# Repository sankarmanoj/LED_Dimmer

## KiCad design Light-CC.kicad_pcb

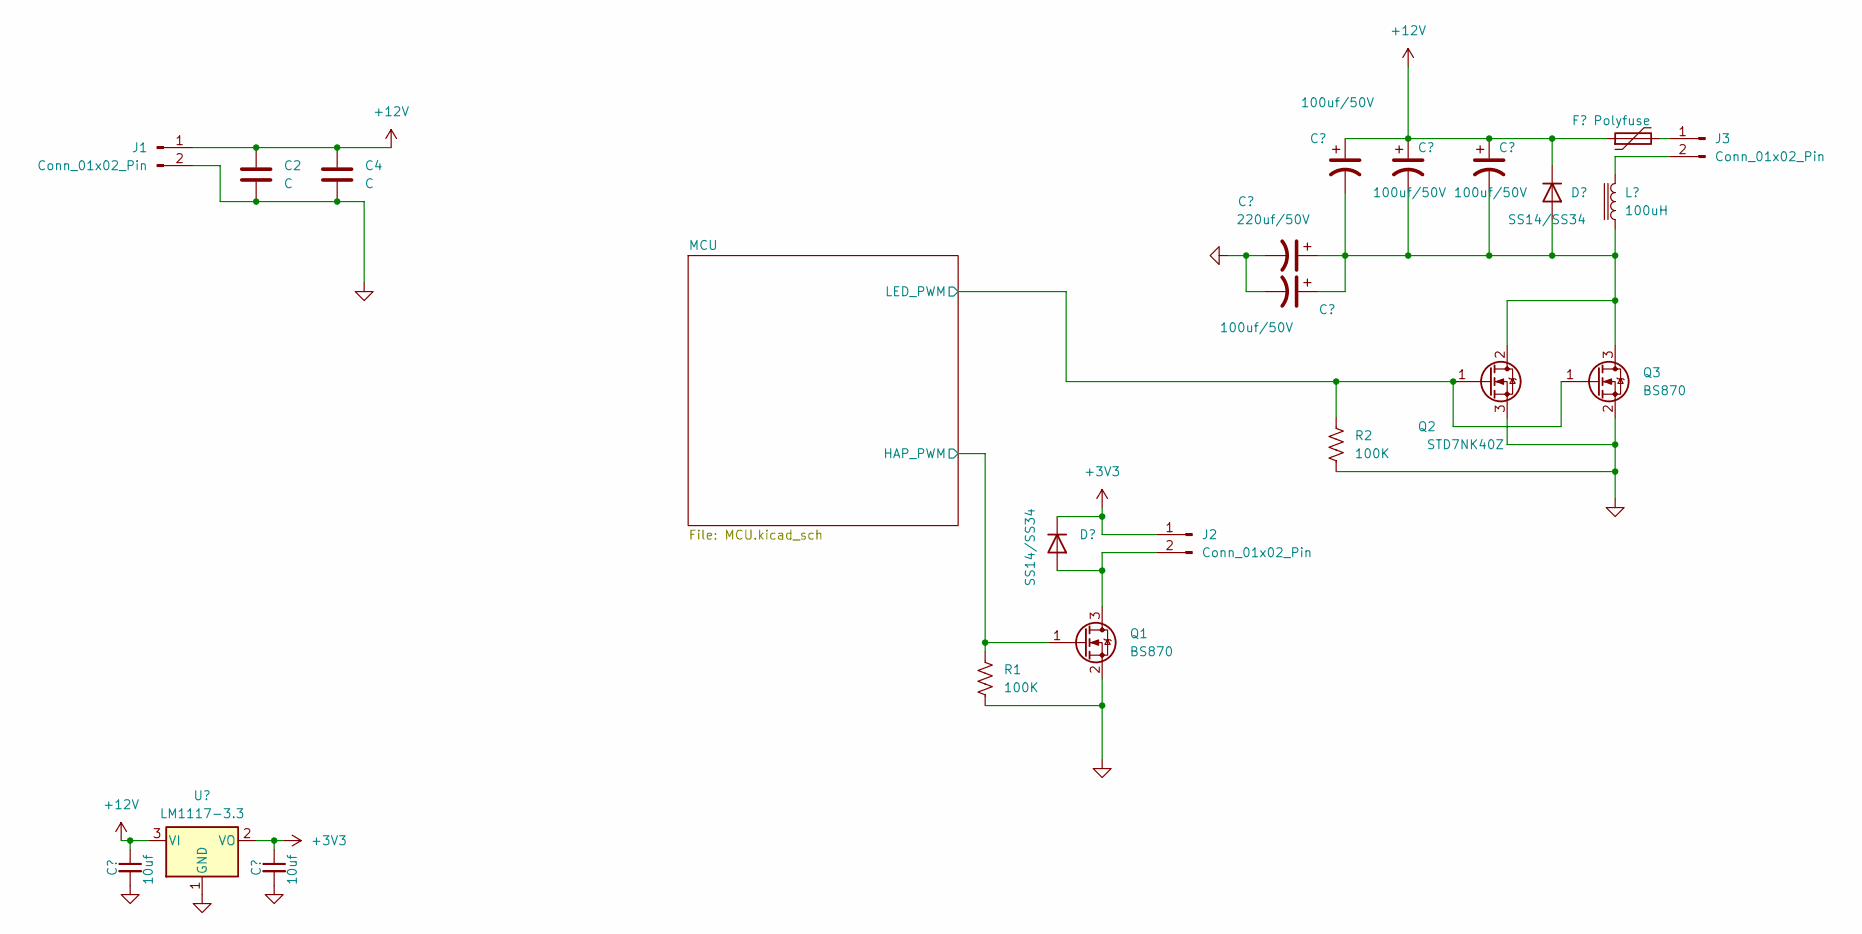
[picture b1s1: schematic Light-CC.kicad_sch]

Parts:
C1, C3: 10uf; C_0805_2012Metric
C2, C4: C; C_0805_2012Metric
C5: 220uf/50V; C_1206_3216Metric
C6, C9: 100uf/50V; C_1206_3216Metric
C7, C8: 100uf/50V; CP_Radial_D5.0mm_P2.50mm
D1, D2: SS14/SS34; D_SMA
F1: Polyfuse; Fuse_1206_3216Metric
J1, J3: Conn_01x02_Pin; SolderWire-0.75sqmm_1x02_P7mm_D1.25mm_OD3.5mm
J2: Conn_01x02_Pin; SolderWire-0.1sqmm_1x02_P3.6mm_D0.4mm_OD1mm_Relief
L1: 100uH; L_Bourns_SRR1260
Q1, Q3: BS870; SOT-23
Q2: STD7NK40Z; TO-252-2
R1, R2: 100K; R_0805_2012Metric
U1: LM1117-3.3; SOT-223-3_TabPin2

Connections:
+3V3: C3.1, D1.1 (K), J2.1, U1.2 (VO); also elsewhere on the board
+12V: C1.1, C2.1, C4.1, C7.1, C8.1, C9.1, D2.1 (K), F1.1, J1.1, U1.3 (VI)
/MCU/HAP_PWM: Q1.1 (G), R1.1; also elsewhere on the board
/MCU/LED_PWM: Q2.1 (G), Q3.1 (G), R2.1; also elsewhere on the board
GND: C1.2, C2.2, C3.2, C4.2, C5.2, C6.2, J1.2, Q1.2 (S), Q2.3 (S), Q3.2 (S), R1.2, R2.2, U1.1 (GND); also elsewhere on the board
unnamed: D1.2 (A), J2.2, Q1.3 (D)
unnamed: C5.1, C6.1, C7.2, C8.2, C9.2, D2.2 (A), L1.1, Q2.2 (D), Q3.3 (D)
unnamed: F1.2, J3.1
unnamed: J3.2, L1.2

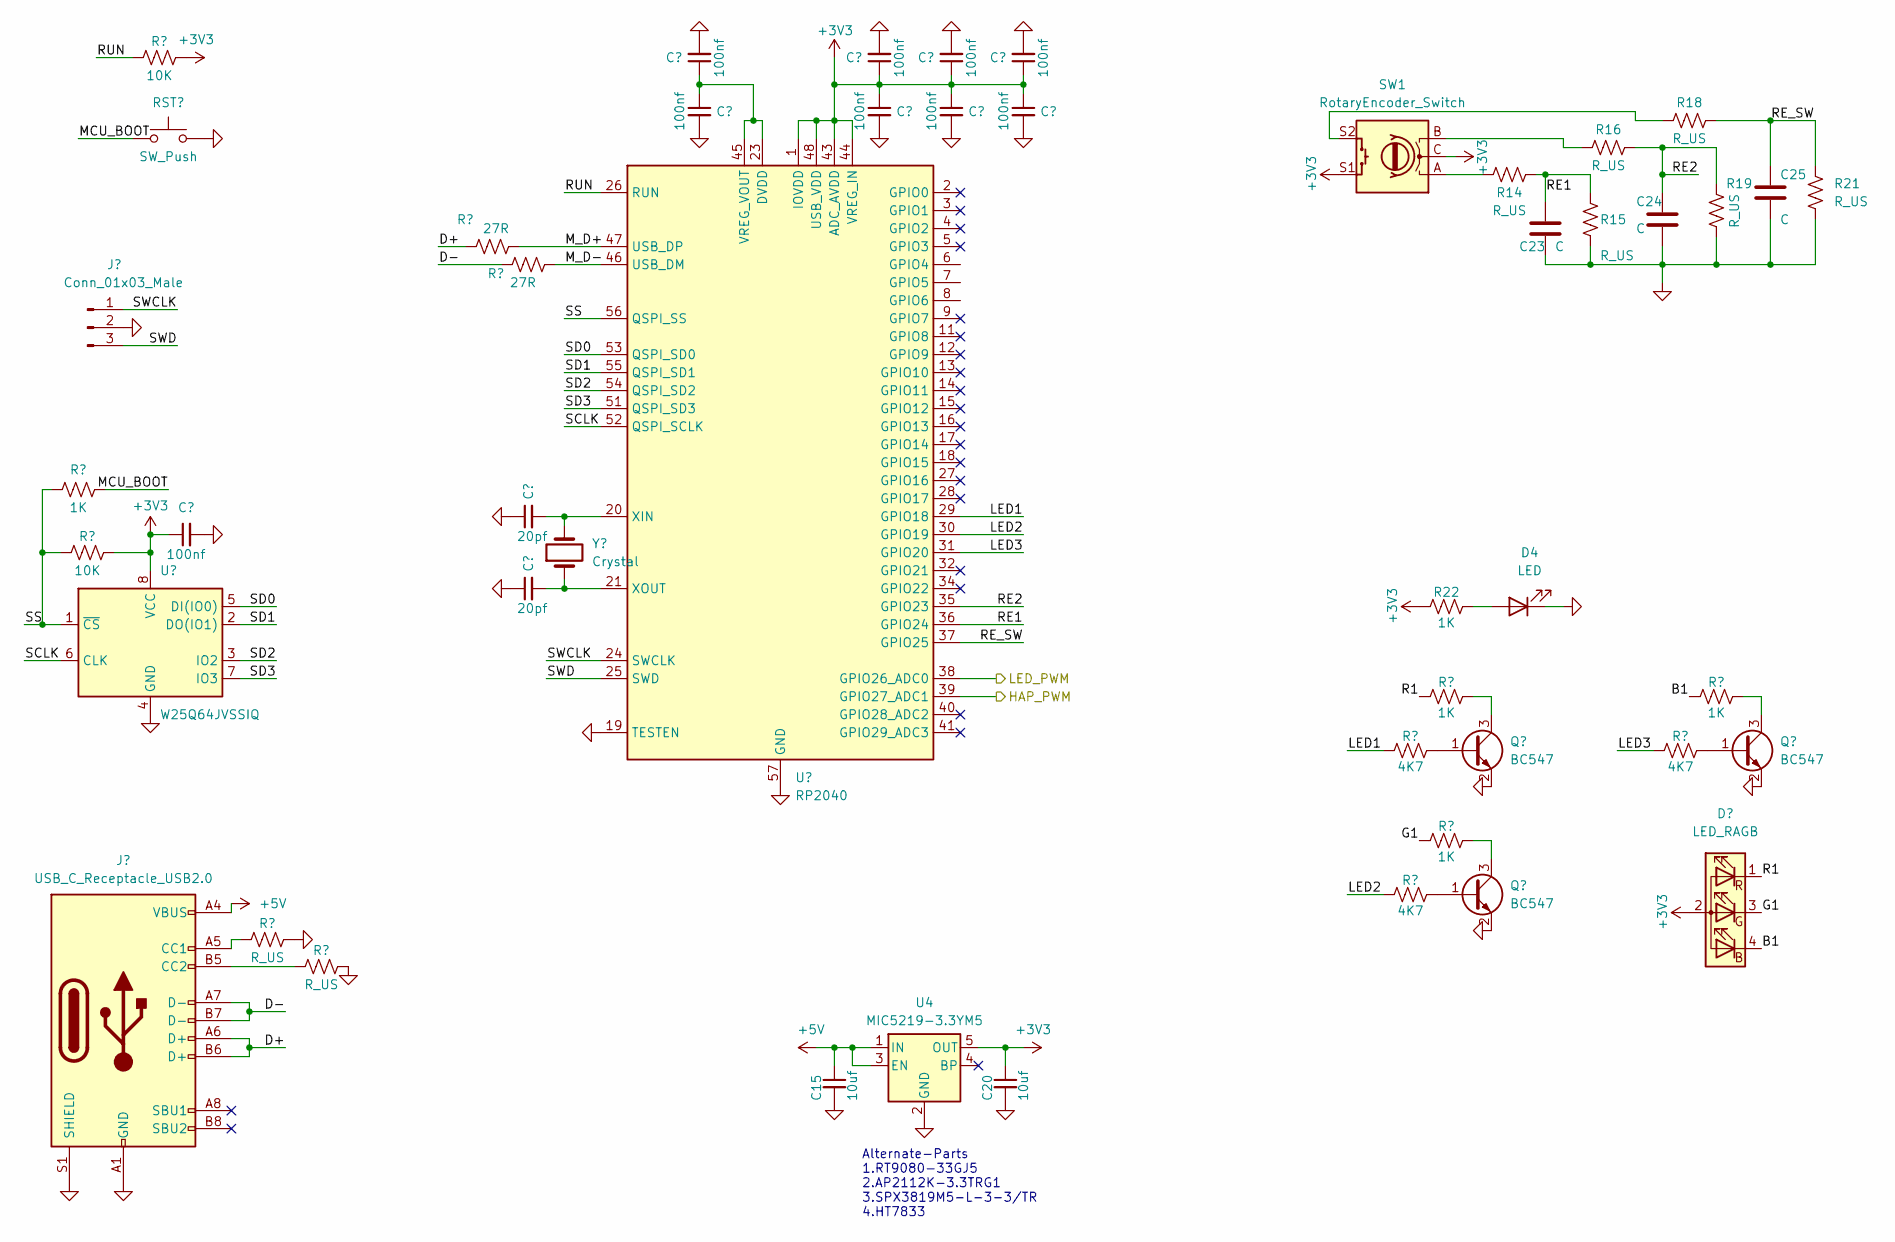
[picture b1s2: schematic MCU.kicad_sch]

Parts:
C10, C13, C14, C16, C17, C18, C19, C21, C22: 100nf; C_0603_1608Metric
C11, C12: 20pf; C_0603_1608Metric
C15, C20: 10uf; C_0805_2012Metric
C23, C24, C25: C; C_0603_1608Metric
D3: LED_RAGB; LED_D5.0mm-4_RGB_Wide_Pins
D4: LED
J4: Conn_01x03_Male; PinHeader_1x03_P2.54mm_Vertical
J5: USB_C_Receptacle_USB2.0; USB_C_Receptacle_Palconn_UTC16-G
Q4, Q5, Q6: BC547; SOT-23
R3, R12, R13, R20, R22: 1K; R_0603_1608Metric
R4, R5: 10K; R_0603_1608Metric
R6, R7, R14, R15, R16, R18, R19, R21: R_US; R_0603_1608Metric
R8, R9: 27R; R_0603_1608Metric
R10, R11, R17: 4K7; R_0603_1608Metric
RST1: SW_Push; SW_SPST_SKQG_WithStem
SW1: RotaryEncoder_Switch; RotaryEncoder_Alps_EC12E-Switch_Vertical_H20mm
U2: W25Q64JVSSIQ; SOIC-8_5.23x5.23mm_P1.27mm
U3: RP2040; QFN-56-1EP_7x7mm_P0.4mm_EP3.2x3.2mm
U4: MIC5219-3.3YM5; SOT-23-5
Y1: Crystal; Crystal_HC49-4H_Vertical

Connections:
+3V3: C10.1, C16.1, C17.1, C18.1, C19.1, C20.1, C21.1, C22.1, D3.2 (A), R4.2, R5.2, R22.1, SW1.C, SW1.S1, U2.8 (VCC), U3.1 (IOVDD), U3.10 (IOVDD), U3.22 (IOVDD), U3.33 (IOVDD), U3.42 (IOVDD), U3.43 (ADC_AVDD), U3.44 (VREG_IN), U3.48 (USB_VDD), U3.49 (IOVDD), U4.5 (OUT); also elsewhere on the board
+5V: C15.1, J5.A4 (VBUS), J5.A9 (VBUS), J5.B4 (VBUS), J5.B9 (VBUS), U4.1 (IN), U4.3 (EN)
/MCU/B1: D3.4 (BK), R20.1
/MCU/D+: J5.A6 (D+), J5.B6 (D+), R8.1
/MCU/D-: J5.A7 (D-), J5.B7 (D-), R9.1
/MCU/G1: D3.3 (GK), R13.1
/MCU/HAP_PWM: U3.39 (GPIO27_ADC1); also elsewhere on the board
/MCU/LED1: R10.1, U3.29 (GPIO18)
/MCU/LED2: R11.1, U3.30 (GPIO19)
/MCU/LED3: R17.1, U3.31 (GPIO20)
/MCU/LED_PWM: U3.38 (GPIO26_ADC0); also elsewhere on the board
/MCU/MCU_BOOT: R3.2, RST1.1
/MCU/M_D+: R8.2, U3.47 (USB_DP)
/MCU/M_D-: R9.2, U3.46 (USB_DM)
/MCU/R1: D3.1 (RK), R12.1
/MCU/RE1: C23.1, R14.1, R15.1, U3.36 (GPIO24)
/MCU/RE2: C24.1, R16.2, R19.1, U3.35 (GPIO23)
/MCU/RE_SW: C25.1, R18.2, R21.1, U3.37 (GPIO25)
/MCU/RUN: R5.1, U3.26 (RUN)
/MCU/SCLK: U2.6 (CLK), U3.52 (QSPI_SCLK)
/MCU/SD0: U2.5 (DI(IO0)), U3.53 (QSPI_SD0)
/MCU/SD1: U2.2 (DO(IO1)), U3.55 (QSPI_SD1)
/MCU/SD2: U2.3 (IO2), U3.54 (QSPI_SD2)
/MCU/SD3: U2.7 (IO3), U3.51 (QSPI_SD3)
/MCU/SS: R3.1, R4.1, U2.1 (~CS), U3.56 (QSPI_SS)
/MCU/SWCLK: J4.1, U3.24 (SWCLK)
/MCU/SWD: J4.3, U3.25 (SWD)
GND: C10.2, C11.1, C12.1, C13.2, C14.2, C15.2, C16.2, C17.2, C18.2, C19.2, C20.2, C21.2, C22.2, C23.2, C24.2, C25.2, D4.1 (K), J4.2, J5.A1 (GND), J5.A12 (GND), J5.B1 (GND), J5.B12 (GND), J5.S1 (SHIELD), Q4.2 (E), Q5.2 (E), Q6.2 (E), R6.2, R7.2, R15.2, R19.2, R21.2, RST1.2, U2.4 (GND), U3.19 (TESTEN), U3.57 (GND), U4.2 (GND); also elsewhere on the board
unnamed: D4.2 (A), R22.2
unnamed: J5.A5 (CC1), R6.1
unnamed: J5.B5 (CC2), R7.1
unnamed: Q4.1 (B), R10.2
unnamed: Q4.3 (C), R12.2
unnamed: Q5.1 (B), R11.2
unnamed: Q5.3 (C), R13.2
unnamed: Q6.1 (B), R17.2
unnamed: Q6.3 (C), R20.2
unnamed: R14.2, SW1.A
unnamed: R16.1, SW1.B
unnamed: R18.1, SW1.S2
unnamed: C13.1, C14.1, U3.23 (DVDD), U3.45 (VREG_VOUT), U3.50 (DVDD)
unnamed: C11.2, U3.20 (XIN), Y1.2
unnamed: C12.2, U3.21 (XOUT), Y1.1

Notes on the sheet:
Alternate-Parts 1.RT9080-33GJ5 2.AP2112K-3.3TRG1 3.SPX3819M5-L-3-3/TR 4.HT7833

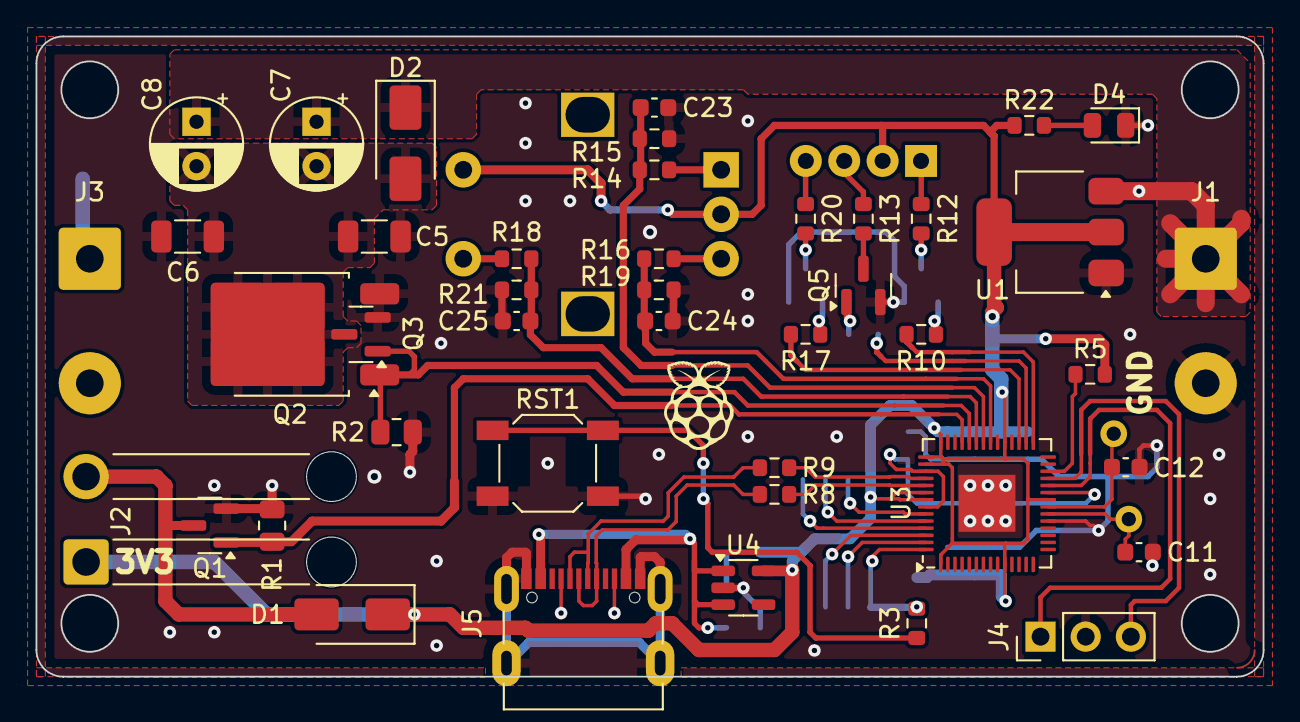
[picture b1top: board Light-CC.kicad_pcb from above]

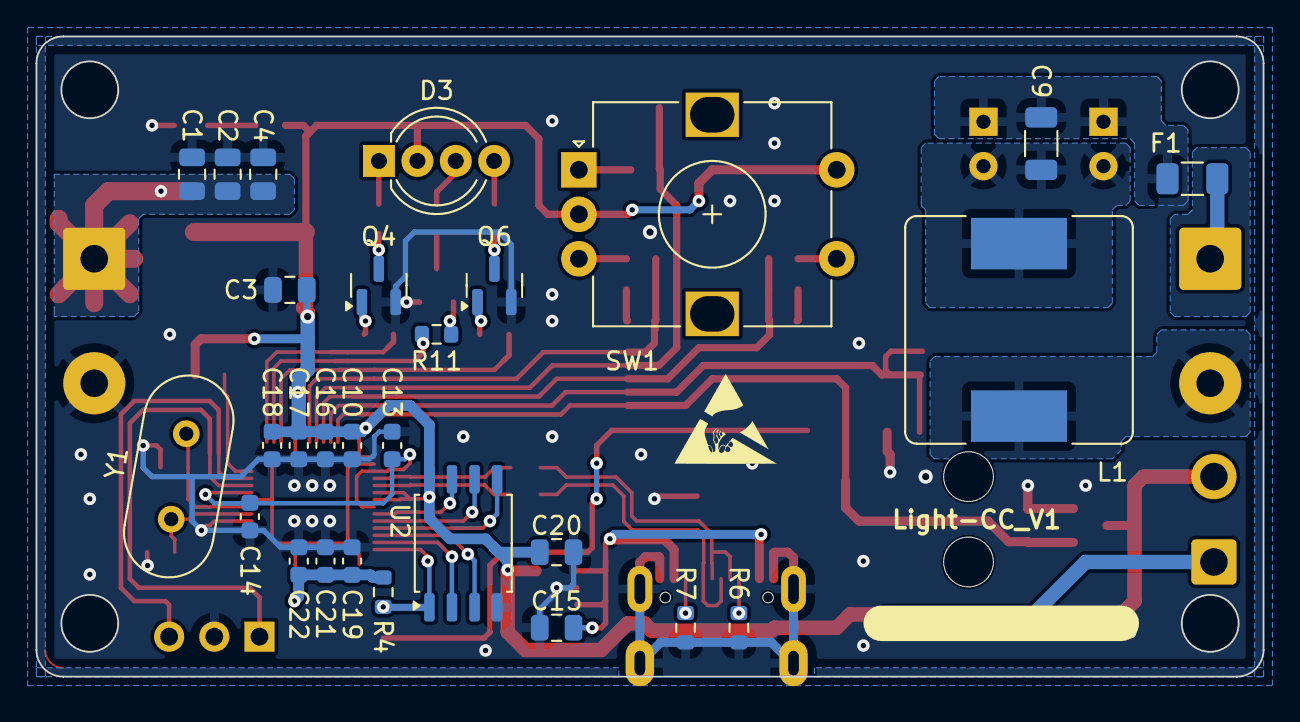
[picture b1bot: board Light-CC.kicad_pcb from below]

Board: 2 copper layers, 69.0 x 36.0 mm, 71 parts (28 on the bottom side), 48 nets.

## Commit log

2024-06-17 Done
2024-06-17 Added PolyFuse to output
2024-06-19 Changed the layout based on Power supply
2024-06-20 Controller Area placement is done
2024-06-20 Layout Routing Beign's
2024-06-21 Layout Routing is 50% complete
2024-06-21 Layout & routing is almost done Logo need to added
2024-06-21 Pwr led added
2024-06-22 Design Completed & Gerber generated
